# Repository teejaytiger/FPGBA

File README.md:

# FPGBA
## An overhaul of the original Gameboy Advance hardware! Features:
1. Simultaneous play + charging (USB-C)
2. FPGA JTAG headers for reprogramming
3. Modular design (Mainboard and daughter boards for the left and right controls)
4. Native support for IPS screens
5. Modern audio (no hiss!)

Still in the early stages! Check back for more later!

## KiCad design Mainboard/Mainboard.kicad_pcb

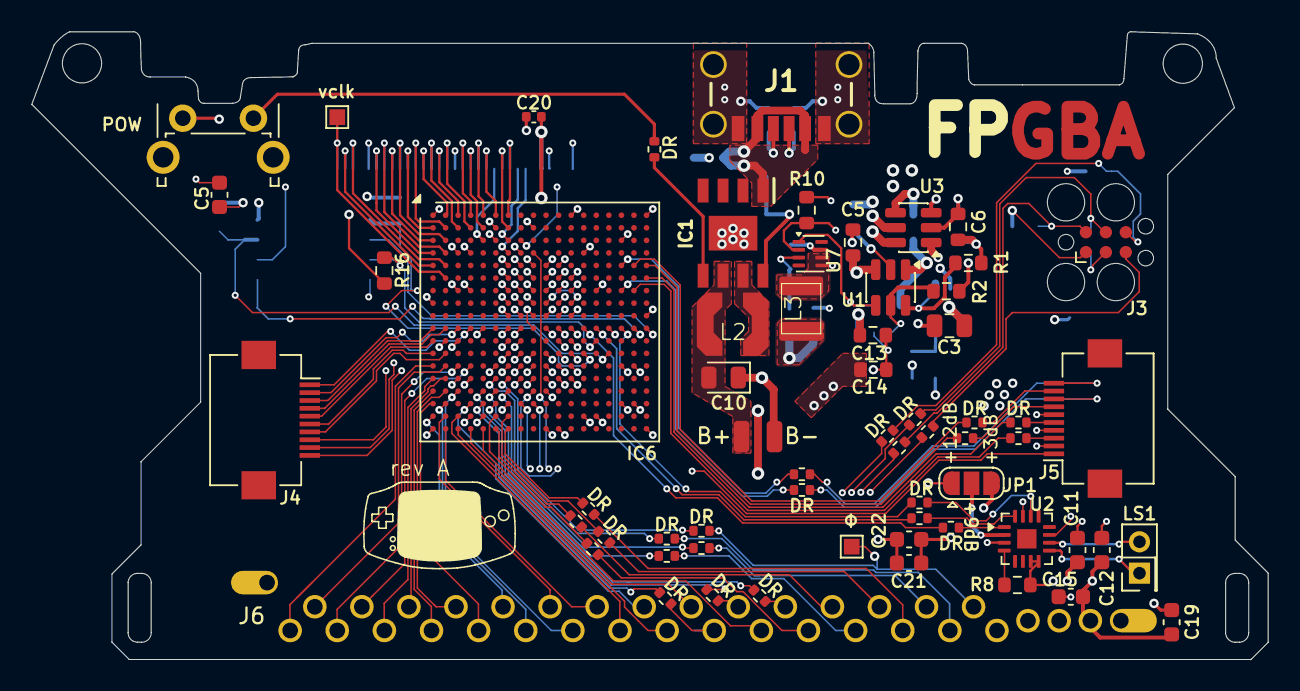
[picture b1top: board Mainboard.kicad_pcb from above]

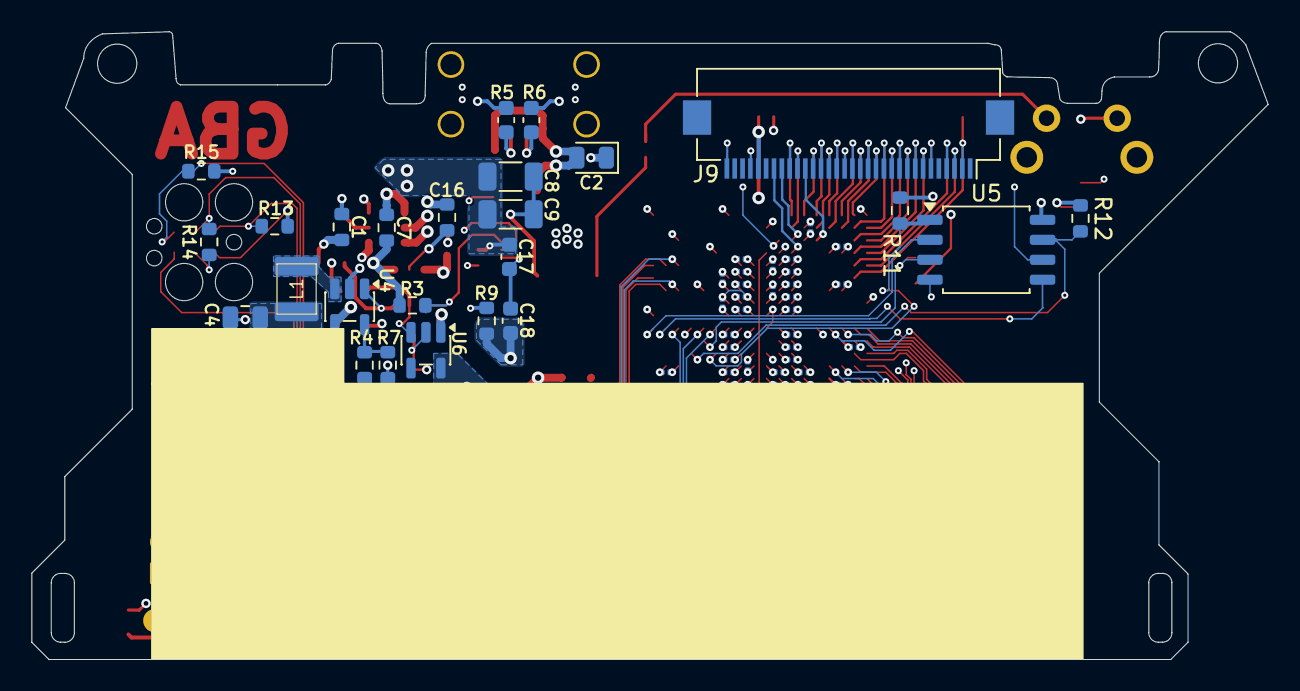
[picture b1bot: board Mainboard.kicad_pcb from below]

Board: 4 copper layers, 78.8 x 40.0 mm, 89 parts (25 on the bottom side), 102 nets.

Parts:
B+: SolderWirePad_1x01_SMD_1x2mm
B-: SolderWirePad_1x01_SMD_1x2mm
C1, C6, C16: 100nF; R_0603_1608Metric
C2, C10: 10uF; LED_0805_2012Metric
C3, C4: 10uF; C_0805_2012Metric
C5, C13, C14: 1uF; R_0603_1608Metric
C5#2: 0.1uF; C_0603_1608Metric
C7: 1nF; R_0603_1608Metric
C8, C9: 22uF; C_1206_3216Metric
C11: .1uF; C_0603_1608Metric
C12, C17, C22: 10uF; C_0603_1608Metric
C15, C19, C21: 100nF; C_0603_1608Metric
C18: 22uF; C_0603_1608Metric
C20: 100nF; C_0402_1005Metric
DR: 22; R_0402_1005Metric
DR#2, DR#3, DR#4, DR#5, DR#6, DR#7, DR#8, DR#9, DR#10, DR#11, DR#12, DR#13, DR#14, DR#15, DR#16, DR#17, DR#18, DR#19, DR#20, DR#21, DR#22, DR#23, DR#24, DR#25: 22; R_0402_1005Metric
IC1: IP5306; SOIC127P600X165-9N
IC6: XC7S50-L1CSGA324I; BGA-324_15x15mm_Layout18x18_P0.8mm
J1: 2479774-2; 24797742
J3: Conn_01x06_Pin; Tag-Connect_TC2030-IDC-FP_2x03_P1.27mm_Vertical
J4: Left Daughter Connector; Hirose_FH12-10S-0.5SH_1x10-1MP_P0.50mm_Horizontal
J5: Right Daughter Connector; Hirose_FH12-10S-0.5SH_1x10-1MP_P0.50mm_Horizontal
J6: CART; AGB Cart Pin
J9: Screen zif FFC/FPC; Hirose_FH12-32S-0.5SH_1x32-1MP_P0.50mm_Horizontal
JP1: Jumper_3_Open; SolderJumper-3_P1.3mm_Open_RoundedPad1.0x1.5mm
L1, L3: 2.2uH; 1206 (metric 2832)
L2: 1uH; LPS4018
LS1: Speaker; PinHeader_2x01_P2.00mm_Vertical
R1, R2, R3: 33k; R_0603_1608Metric
R4: 180k; R_0603_1608Metric
R5, R6: 5.1k; C_0603_1608Metric
R7: 150k; R_0603_1608Metric
R8: 1M; R_0603_1608Metric
R9: 453k; R_0603_1608Metric
R10: 100k; R_0603_1608Metric
R11, R12, R16: 10k; R_0603_1608Metric
R13, R14, R15: 4.7k; R_0603_1608Metric
SW1: POW; SW_Tactile_SPST_Angled_PTS645Vx58-2LFS
U1: LM3880; SOT-23-6
U2: MAX98357A; TQFN-16-1EP_3x3mm_P0.5mm_EP1.23x1.23mm
U3: TPS22917DBV; SOT-23-6
U4: TLV62569DBV; SOT-23-5
U5: W25Q128JVS; SOIC-8_5.3x5.3mm_P1.27mm
U6: TLV75518PDBV; SOT-23-5
U7: TPS62822DLC; Texas_VSON-HR-8_1.5x2mm_P0.5mm
vclk: test; TestPoint_Pad_1.0x1.0mm
Φ: test; TestPoint_Pad_1.0x1.0mm

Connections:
/FPGA/A16: IC6.U1 (IO_L14N_T2_SRCC_34), J6.22
/FPGA/A17: IC6.T1 (IO_L14P_T2_SRCC_34), J6.23
/FPGA/A18: IC6.R2 (IO_L12P_T1_MRCC_34), J6.24
/FPGA/A19: IC6.R1 (IO_L12N_T1_MRCC_34), J6.25
/FPGA/A20: IC6.P2 (IO_L11P_T1_SRCC_34), J6.26
/FPGA/A21: IC6.P1 (IO_L11N_T1_SRCC_34), J6.27
/FPGA/A22: IC6.N4 (IO_L10N_T1_34), J6.28
/FPGA/A23: IC6.N3 (IO_L9P_T1_DQS_34), J6.29
/FPGA/AD0: DR#14.1, DR#14.2, IC6.U7 (IO_L24P_T3_34), J6.6
/FPGA/AD1: DR#12.1, DR#12.2, IC6.R6 (IO_L23N_T3_34), J6.7
/FPGA/AD2: DR#22.1, DR#22.2, IC6.V6 (IO_L20N_T3_34), J6.8
/FPGA/AD3: DR#18.1, DR#18.2, IC6.U6 (IO_L24N_T3_34), J6.9
/FPGA/AD4: DR#20.1, DR#20.2, IC6.T6 (IO_L22P_T3_34), J6.10
/FPGA/AD5: IC6.V5 (IO_L17P_T2_34), J6.11
/FPGA/AD6: DR#4.1, DR#4.2, IC6.R5 (IO_L21P_T3_DQS_34), J6.12
/FPGA/AD7: DR#17.1, DR#17.2, IC6.T5 (IO_L22N_T3_34), J6.13
/FPGA/AD8: IC6.V4 (IO_L17N_T2_34), J6.14
/FPGA/AD9: IC6.V3 (IO_L16P_T2_34), J6.15
/FPGA/AD10: IC6.T4 (IO_L21N_T3_DQS_34), J6.16
/FPGA/AD11: IC6.U3 (IO_L15P_T2_DQS_34), J6.17
/FPGA/AD12: IC6.V2 (IO_L16N_T2_34), J6.18
/FPGA/AD13: IC6.R3 (IO_L13P_T2_MRCC_34), J6.19
/FPGA/AD14: IC6.U2 (IO_L15N_T2_DQS_34), J6.20
/FPGA/AD15: IC6.T2 (IO_L13N_T2_MRCC_34), J6.21
/FPGA/CLS: IC6.A7 (IO_L1N_T0_AD4N_35), J9.24 (CLS)
/FPGA/CS: DR#15.1, DR#15.2, IC6.V7 (IO_L20P_T3_34), J6.5
/FPGA/CS2: IC6.N2 (IO_L9N_T1_DQS_34), J6.30
/FPGA/DCLK: IC6.F2 (IO_L18P_T2_35), J9.2 (DCLK), vclk.1
/FPGA/IRQ/DREQ: IC6.N1 (IO_L8N_T1_34), J6.31
/FPGA/LDB1: IC6.C5 (IO_L2P_T0_AD12P_35), J9.22 (LDB1)
/FPGA/LDB2: IC6.A6 (IO_L4N_T0_35), J9.21 (LDB2)
/FPGA/LDB3: IC6.A5 (IO_L9P_T1_DQS_AD7P_35), J9.20 (LDB3)
/FPGA/LDB4: IC6.B5 (IO_L2N_T0_AD12N_35), J9.19 (LDB4)
/FPGA/LDB5: IC6.A4 (IO_L9N_T1_DQS_AD7N_35), J9.18 (LDB5)
/FPGA/LDG1: IC6.B4 (IO_L7N_T1_AD6N_35), J9.16 (LDG1)
/FPGA/LDG2: IC6.A3 (IO_L10P_T1_AD15P_35), J9.15 (LDG2)
/FPGA/LDG3: IC6.B3 (IO_L8N_T1_AD14N_35), J9.14 (LDG3)
/FPGA/LDG4: IC6.A2 (IO_L10N_T1_AD15N_35), J9.13 (LDG4)
/FPGA/LDG5: IC6.B2 (IO_L11N_T1_SRCC_35), J9.12 (LDG5)
/FPGA/LDR1: IC6.B1 (IO_L12N_T1_MRCC_35), J9.11 (LDR1)
/FPGA/LDR2: IC6.C2 (IO_L11P_T1_SRCC_35), J9.10 (LDR2)
/FPGA/LDR3: IC6.C1 (IO_L12P_T1_MRCC_35), J9.9 (LDR3)
/FPGA/LDR4: IC6.D2 (IO_L16N_T2_35), J9.8 (LDR4)
/FPGA/LDR5: IC6.D1 (IO_L14N_T2_SRCC_35), J9.7 (LDR5)
/FPGA/LP: IC6.E1 (IO_L14P_T2_SRCC_35), J9.3 (LP)
/FPGA/MOD: IC6.D7 (IO_L3P_T0_DQS_AD5P_35), J9.26 (MOD)
/FPGA/PHI: DR.1, DR.2, IC6.P7 (IO_25_34), J6.2, Φ.1
/FPGA/PS: IC6.E2 (IO_L16P_T2_35), J9.4 (PS)
/FPGA/RD: DR#11.1, DR#11.2, IC6.R7 (IO_L23P_T3_34), J6.4
/FPGA/SPL: IC6.B7 (IO_L4P_T0_35), J9.23 (SPL)
/FPGA/SPS: IC6.C7 (IO_L3N_T0_DQS_AD5N_35), J9.25 (SPS)
/FPGA/WR: DR#16.1, DR#16.2, IC6.P6 (IO_L19P_T3_34), J6.3
/FPGBA Charging/USB5VIN: C2.2, IC1.1 (VIN), J1.A9 (VBUS_1), J1.B9 (VBUS_2)
/FPGBA_Power/flag1: R1.2, U1.6 (FLAG1), U4.1 (EN)
/FPGBA_Power/flag2: R2.2, U1.5 (FLAG2), U6.3 (EN)
/FPGBA_Power/flag3: R3.2, U1.4 (FLAG3), U7.1 (EN)
CCLK_0: IC6.C8 (CCLK_0), U5.6 (CLK)
D00_MOSI: IC6.K17 (IO_L1P_T0_D00_MOSI_14), U5.5 (DI/IO_{0})
D01: IC6.K18 (IO_L1N_T0_D01_DIN_14), U5.2 (DO/IO_{1})
D02: IC6.L14 (IO_L2P_T0_D02_14), R16.2, U5.3 (~WP/IO_{2})
D03: IC6.M15 (IO_L2N_T0_D03_14), R12.2, U5.7 (~HOLD/~RESET/IO_{3})
FCS_B: IC6.M13 (IO_L6P_T0_FCS_B_14), R11.2, U5.1 (~CS)
GND: B-.1, C1.1, C2.1, C3.1, C4.2, C5.1, C5#2.2, C6.1, C10.1, C11.2, C12.2, C13.1, C14.1, C15.2, C16.1, C17.1, C18.1, C19.2, C20.2, C21.2, C22.2, IC1.9 (EP), IC6.A1 (GND_1), IC6.A12, IC6.A18, IC6.B9, IC6.C6, IC6.C16, IC6.D3, IC6.D13, IC6.E8, IC6.E10, IC6.F7, IC6.F9, IC6.F11, IC6.G4, IC6.G8, IC6.G10, IC6.G12, IC6.G14, IC6.H1, IC6.H7, IC6.H9 (GNDADC_0), IC6.H11, IC6.J8, IC6.J9 (VREFN_0), IC6.J10 (VP_0), IC6.J12, IC6.J18, IC6.K5, IC6.K7, IC6.K9 (VN_0), IC6.K10 (VREFP_0), IC6.K11, IC6.K15, IC6.L2, IC6.L8, IC6.L12, IC6.M7, IC6.M9, IC6.M11, IC6.N6, IC6.N8, IC6.N10, IC6.N12, IC6.N16, IC6.P3, IC6.P9, IC6.P11, IC6.R10, IC6.T7, IC6.T17, IC6.U4, IC6.U14, IC6.V1, IC6.V11, IC6.V18, J1.1 (MH1), J1.2 (MH2), J1.3 (MH3), J1.4 (MH4), J1.A12 (GND_1), J1.B12 (GND_2), J3.3, J4.8, J4.9, J4.10, J5.2, J5.4, J5.6, J9.6 (DGND), J9.17 (LDG0), J9.29 (VSS), J9.32 (AGND), JP1.1 (A), R5.2, R6.2, R7.2, R10.2, R14.1, SW1.1 (1_1), U1.2 (GND), U2.3 (GND), U2.11 (GND), U2.15 (GND), U3.2 (GND), U4.2 (GND), U5.4 (GND), U6.2 (GND), U7.3 (AGND), U7.5 (PGND)
unnamed: B+.1, C10.2, IC1.6 (BAT), L2.2
unnamed: IC1.7 (SW), L2.1
unnamed: C8.1, C9.1, IC1.8 (VOUT)
unnamed: IC6.K4 (IO_L1P_T0_34), J4.1
unnamed: IC6.K2 (IO_L2N_T0_34), J4.4
unnamed: IC6.K3 (IO_L2P_T0_34), J4.2
unnamed: IC6.L1 (IO_L3N_T0_DQS_34), J4.5
unnamed: IC6.K1 (IO_L3P_T0_DQS_34), J4.3
unnamed: IC6.M2 (IO_L7N_T1_34), J4.7
unnamed: IC6.M1 (IO_L8P_T1_34), J4.6
unnamed: DR#2.1, DR#2.2, IC6.E17 (IO_L10N_T1_AD11N_15), J5.9
unnamed: DR#25.1, DR#25.2, IC6.E16 (IO_L10P_T1_AD11P_15), J5.10
unnamed: DR#7.1, DR#7.2, IC6.G17 (IO_L14N_T2_SRCC_15), J5.3
unnamed: DR#5.1, DR#5.2, IC6.G16 (IO_L14P_T2_SRCC_15), J5.8
unnamed: DR#10.1, DR#10.2, IC6.E18 (IO_L16N_T2_15), J5.7
unnamed: DR#19.1, DR#19.2, IC6.F18 (IO_L16P_T2_15), J5.5
unnamed: J1.A5 (CC1), R5.1
unnamed: J1.B5 (CC2), R6.1
unnamed: JP1.2 (C), U2.2 (GAIN_SLOT)
unnamed: LS1.2, U2.10 (OUTN)
unnamed: LS1.1, U2.9 (OUTP)
unnamed: R8.2, U2.4 (~SD_MODE)
unnamed: C7.2, U3.4 (CT)
unnamed: R4.2, R7.1, U4.5 (FB)
unnamed: L1.1, U4.3 (SW)
unnamed: R9.2, R10.1, U7.2 (FB)
unnamed: L3.1, U7.6 (SW)
REF1V: C4.1, IC6.E7 (VCCINT_1), IC6.E9 (VCCINT_2), IC6.E11 (VCCINT_3), IC6.F8 (VCCINT_4), IC6.F10 (VCCINT_5), IC6.G7 (VCCINT_6), IC6.G9 (VCCINT_7), IC6.G11 (VCCINT_8), IC6.H8 (VCCINT_9), IC6.J7 (VCCINT_10), IC6.J11 (VCCINT_11), IC6.K8 (VCCINT_12), IC6.L7 (VCCBRAM_1), IC6.L11 (VCCINT_13), IC6.M8 (VCCINT_14), IC6.M10 (VCCINT_15), IC6.N7 (VCCBRAM_2), IC6.N9 (VCCINT_16), IC6.N11 (VCCINT_17), IC6.P8 (VCCINT_18), IC6.P10 (VCCINT_19), L1.2, R4.1
SPKBCLK: DR#9.1, DR#9.2, IC6.K14 (IO_L23P_T3_15), U2.16 (BCLK)
SPKDIN: DR#21.1, DR#21.2, IC6.K13 (IO_25_15), U2.1 (DIN)
SPKLRC: DR#23.1, DR#23.2, IC6.K16 (IO_L19P_T3_15), U2.14 (LRCLK)
SYS_5V: C1.2, C6.2, C7.1, C8.2, C9.2, C17.2, R1.1, R2.1, R3.1, U1.1 (VCC), U3.1 (VIN), U3.3 (ON), U7.7 (VIN)
TCK_0: DR#3.1, DR#3.2, IC6.D9 (TCK_0), J3.4, R14.2
TDI_0: DR#8.1, DR#8.2, IC6.R9 (TDI_0), J3.6, R15.1
TDO_0: DR#24.1, DR#24.2, IC6.T8 (TDO_0), J3.5
TMS_0: DR#13.1, DR#13.2, IC6.T9 (TMS_0), J3.2, R13.2
VREF1V8: C14.2, IC6.F12 (VCCAUX_1), IC6.H10 (VCCADC_0), IC6.H12 (VCCAUX_2), IC6.K12 (VCCAUX_3), IC6.M12 (VCCAUX_4), IC6.P12 (VCCAUX_5), U6.5 (OUT)
VREF3V3: C5#2.1, C11.1, C12.1, C15.1, C18.2, C19.1, C20.1, C21.1, C22.1, IC6.B6 (VCCO_35_1), IC6.D4, IC6.D8 (VCCO_0_1), IC6.G3 (VCCO_35_3), IC6.L3 (VCCO_34_1), IC6.N17 (VCCO_14_1), IC6.P4 (VCCO_34_2), IC6.T16 (VCCO_14_2), IC6.U5 (VCCO_34_3), IC6.U13 (VCCO_14_3), IC6.V10 (VCCO_0_2), J3.1, J5.1, J6.1, J6.C1, J6.S1, J9.28 (VDD), JP1.3 (B), L3.2, R8.1, R9.1, R11.1, R12.1, R13.1, R15.2, R16.1, U2.7 (VDD), U2.8 (VDD), U5.8 (VCC)
VREF5V: C3.2, C5.2, C13.2, C16.2, U1.3 (EN), U3.5 (QOD), U3.6 (VOUT), U4.4 (VIN), U6.1 (IN)

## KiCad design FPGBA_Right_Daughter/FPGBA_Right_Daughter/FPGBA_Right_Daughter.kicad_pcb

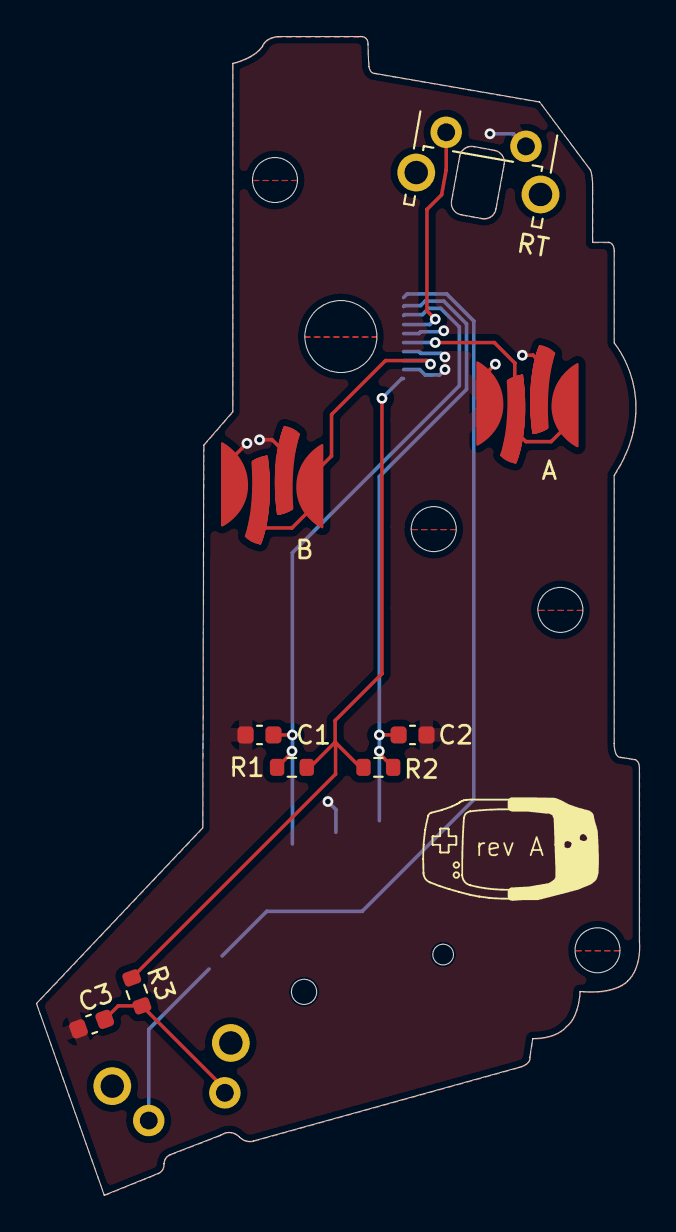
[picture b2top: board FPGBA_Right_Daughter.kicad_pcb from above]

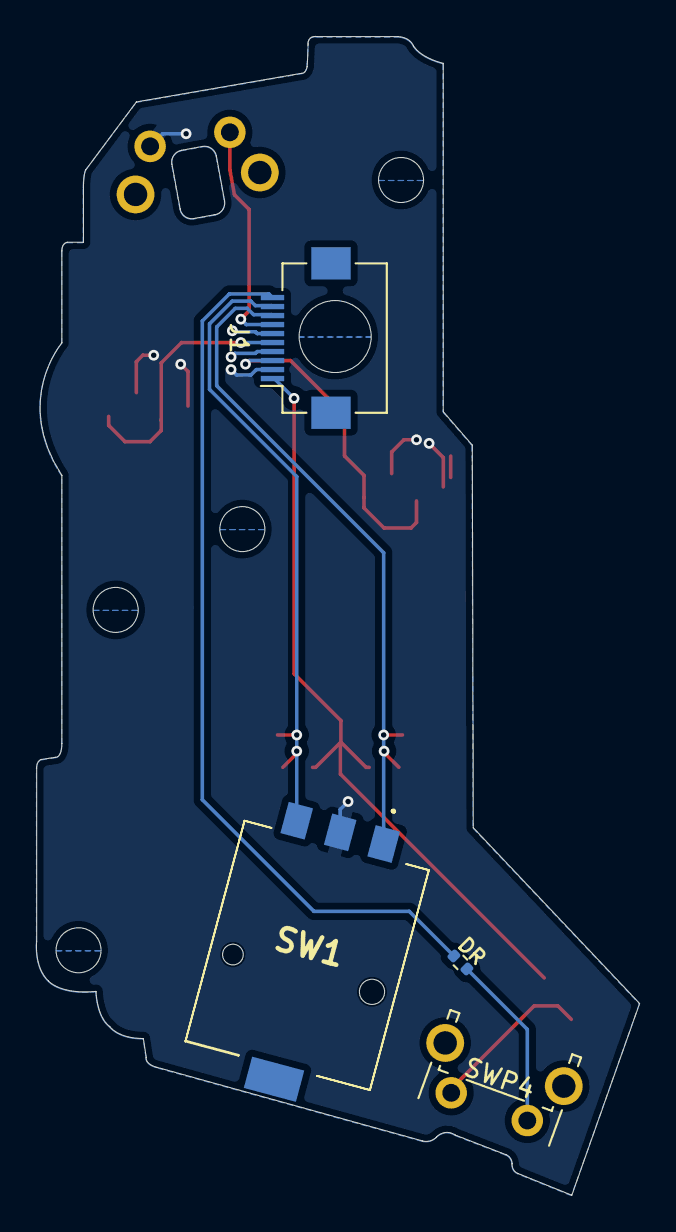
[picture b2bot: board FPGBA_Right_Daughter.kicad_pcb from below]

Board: 2 copper layers, 33.5 x 64.4 mm, 13 parts (4 on the bottom side), 9 nets.

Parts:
A: A; AGB AB
B: B; AGB AB
C1, C2, C3: 10nF; C_0603_1608Metric
DR: 22; R_0402_1005Metric
J1: Mainboard Connector; Hirose_FH12-10S-0.5SH_1x10-1MP_P0.50mm_Horizontal
R1, R2, R3: 10k; R_0603_1608Metric
RT: RS; SW_Tactile_SPST_Angled_PTS645Vx58-2LFS
SW1: RotaryEncoder; EVQVVD00203B
SWP4: RS; SW_Tactile_SPST_Angled_PTS645Vx58-2LFS

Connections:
/BTN_A: A.1, J1.5
/BTN_B: B.1, J1.3
/BTN_RS: J1.7, RT.1
GND: A.2, B.2, C1.2, C2.2, C3.2, J1.2, J1.4, J1.6, RT.2, SW1.C
unnamed: C3.1, R3.2, SWP4.2
unnamed: C1.1, J1.8, R1.2, SW1.A
unnamed: C2.1, J1.9, R2.2, SW1.B
unnamed: DR.1, DR.2, J1.10, SWP4.1
VREF3V3: J1.1, R1.1, R2.1, R3.1

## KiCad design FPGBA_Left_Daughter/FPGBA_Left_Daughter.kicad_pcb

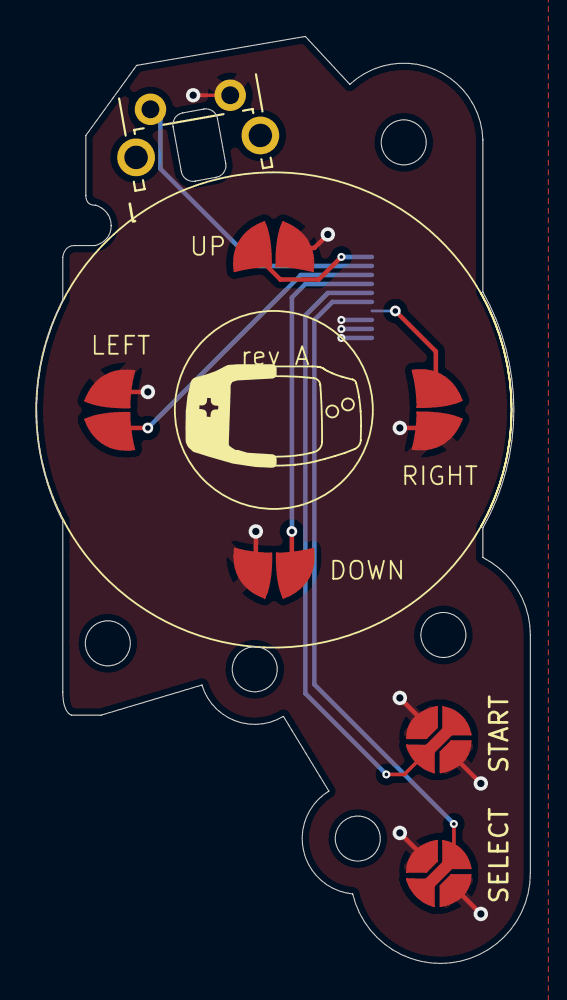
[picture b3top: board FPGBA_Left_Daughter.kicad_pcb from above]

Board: 2 copper layers, 27.4 x 51.5 mm, 8 parts (1 on the bottom side), 8 nets.

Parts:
SWP2: SELECT; AGB ST SL
SWP3: START; AGB ST SL
SWP4: RIGHT; ABG DPAD
SWP5: LEFT; ABG DPAD
SWP6: UP; ABG DPAD
SWP7: DOWN; ABG DPAD
SWP9: L; SW_Tactile_SPST_Angled_PTS645Vx58-2LFS
U1: Hirose_FH12-10S-0.5SH_1x10-1MP_P0.50mm_Horizontal

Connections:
/P2: SWP2.1, U1.6 (P2)
/P3: SWP3.1, U1.5 (P3)
/P4: SWP4.1, U1.7 (P4)
/P5: SWP5.1, U1.3 (P5)
/P6: SWP6.1, U1.1 (P6)
/P7: SWP7.1, U1.4 (P7)
/P9: SWP9.1, U1.2 (P9)
GND: SWP2.2, SWP3.2, SWP4.2, SWP5.2, SWP6.2, SWP7.2, SWP9.2, U1.8 (GND), U1.9 (GND), U1.10 (GND)
